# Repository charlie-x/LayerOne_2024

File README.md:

# LayerOne_2024
Repo for LayerOne 2024

# L1 Pov Spinner

## What is the Pov Spinner?

The Pov Spinner is an electronic fidget spinner that displays words and patterns via LED's when spinning. It was part of the LayerOne 2024 Conference badge.

## What is needed to change the code on the Spinner?

* Code from repo
* Computer
* AVR programming device
* Build software
* Flash software
* Device drivers

# Code from repo

Clone the git repo or download the zip of the repo

## git clone
```
git clone https://github.com/charlie-x/LayerOne_2024.git
```

## Download zip

```
wget https://github.com/charlie-x/LayerOne_2024/archive/refs/heads/main.zip
```

## Edit the code

Open the **L12024POV.cproj** project file.

The text and animation code is located in **main.c**.

Once the desired changes are complete, run the **build**. This will output the build files into the **Debug** folder.  

The **L12024POV.hex** file created is what will be used to flash the spinner.

## AVR programing device

**NOTE: Any AVR programmer should work.**

The LayerOne attendees were able to obtain a **Kraken** AVR programmer to use for this purpose which is an avrisp/mkii/avr dragon/usbasp.

Kraken based on this board: 

https://www.fischl.de/usbasp/

### Arduino as an AVR programmer

Alternatively, and Ardunio can be used to program the device:

https://docs.arduino.cc/built-in-examples/arduino-isp/ArduinoISP/

https://www.amazon.com/CANADUINO-USBtinyISP-Programmer-Compatible-Arduino/dp/B0751LJH3Z

## Build Software

Either use Microchip Studio or avr-gcc to build it.

### *nix

Install **avr-gcc** via the **gcc-avr** package

sudo apt-get install binutils gcc-avr avr-libc uisp avrdude flex byacc bison

### Windows

https://www.microchip.com/en-us/tools-resources/develop/microchip-studio

### Mac

port

https://ports.macports.org/port/avr-gcc/

homebrew

https://github.com/osx-cross/homebrew-avr

for avr-gcc's use the makefile

## Flashing the board

**NOTE: The kraken needs avrdude, it is not supported in microchip studio.**

### *nix / Windows / Mac - avrdude

AVRDUDE - is a program for downloading and uploading the on-chip memories of Microchip’s AVR microcontrollers.

Flash the board with the compiled **hex** file to device

https://github.com/avrdudes/avrdude/releases

```
avrdude -c usbasp -p t4313 -v -B 3 -U flash:w:..\LayerOne_2024-main\LayerOne_2024-main\L1_POVSpinner\L12024POV\Debug\L12024POV.hex
```

### Windows - atprogram

atprogram - is a program that comes with Microchip Studio

```
atprogram -cl 200khz -v -d attiny4313 -t atmelice -i isp chiperase
atprogram -cl 200khz -v -d attiny4313 -t atmelice -i isp program -f L12024POV\Release\L12024POV.elf
```

#### Device Drivers for Windows

Zadig is a Windows application that installs generic USB drivers, such as WinUSB, libusb-win32/libusb0.sys or libusbK, to help you access USB devices that can be found here:
https://zadig.akeo.ie/#

Install the **libusbK** driver

## Spinner Pinouts for programming

The device has the Ground pin labeld as **G**. 

## Notes on modifiying the code

The image folder are made of 12xN high 1 bit png's and the imageConvert tool spits them out as a header file, just include them and use drawImage

imageConvert <in.png> <out.h> <label>

use <label> to pass into drawImage use #include <out.h> (with the right name) in the main.c

interrupt driven from a hall effect sensor, triggers the loops to draw and calcs an RPM then it goes into sleep after the effect is drawn, the hall effect can wake it up, but to save battery pressing the button wakes the cpu up again

the slider switch needs to be be in the furthest away position from the programming pads, match the G to gnd on the programmer..

==============================================================================

calculate x/y

30 is 360/nuber of leds around, which is speed dependant  so used the number of leds vertically

  angle_radians = ( led_number * 30 *pi / 180  )

  x_inner = radius * cos ( angle_radius )
  y_inner = radius * cos ( angle_radius )

distance...

  distance = sqrt( (dx^2) + (dy^2))

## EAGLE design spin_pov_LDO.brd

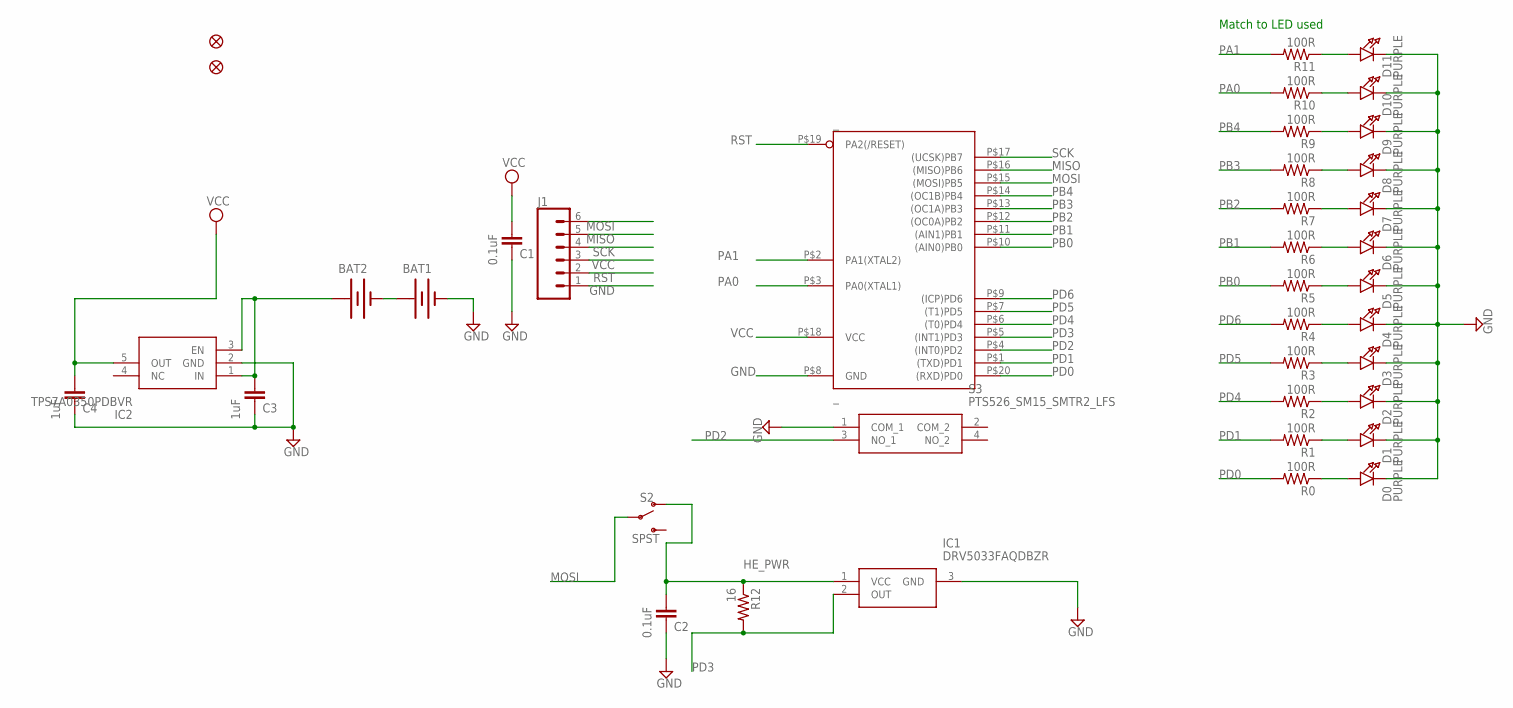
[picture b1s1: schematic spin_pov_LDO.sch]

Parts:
AFID1, AFID2: FIDUCIAL""; FIDUCIAL_1MM
BAT1, BAT2: SPARKFUN_BATTERYSPARKFUN_BATTCOMM_20MM_LINX; SPARKFUN_BATTCOM_20MM_LINX
C1, C2: 0.1uF; 0805
C3, C4: 1uF; 0805
D0, D1, D2, D3, D4, D5, D6, D7, D8, D9, D10, D11: PURPLE; CHIPLED_0805_NOOUTLINE
IC1: DRV5033FAQDBZR; SOT95P237X112-3N
IC2: TPS7A0350PDBVR; SOT95P280X145-5N
J1: CONN_06SMD-FEMALE-V2; 1X06-SMD-FEMALE
R0, R1, R2, R3, R4, R5, R6, R7, R8, R9, R10, R11: 100R; 0805
R12: 16; 0805
S2: SPST; SWITCH_SPST_SMD_A
S3: PTS526_SM15_SMTR2_LFS; PTS526SM15SMTR2LFS
_: _; MLF20

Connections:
GND: BAT1.2 (-), C1.2, C2.2, C3.2, C4.2, D0.C, D1.C, D2.C, D3.C, D4.C, D5.C, D6.C, D7.C, D8.C, D9.C, D10.C, D11.C, IC1.3 (GND), IC2.2 (GND), J1.1, S3.1 (COM_1), _.P$8 (GND)
HE_PWR: C2.1, IC1.1 (VCC), R12.1, S2.1 (O)
MISO: J1.5, _.P$16 ((MISO)PB6)
MOSI: J1.6, S2.2, _.P$15 ((MOSI)PB5)
unnamed: BAT2.1 (+), C3.1, IC2.1 (IN), IC2.3 (EN)
unnamed: BAT1.1 (+), BAT2.2 (-)
unnamed: D0.A, R0.1
unnamed: D1.A, R1.1
unnamed: D2.A, R2.1
unnamed: D3.A, R3.1
unnamed: D4.A, R4.1
unnamed: D5.A, R5.1
unnamed: D6.A, R6.1
unnamed: D7.A, R7.1
unnamed: D8.A, R8.1
unnamed: D9.A, R9.1
unnamed: D10.A, R10.1
unnamed: D11.A, R11.1
PA0: R10.2, _.P$3 (PA0(XTAL1))
PA1: R11.2, _.P$2 (PA1(XTAL2))
PB0: R5.2, _.P$10 ((AIN0)PB0)
PB1: R6.2, _.P$11 ((AIN1)PB1)
PB2: R7.2, _.P$12 ((OC0A)PB2)
PB3: R8.2, _.P$13 ((OC1A)PB3)
PB4: R9.2, _.P$14 ((OC1B)PB4)
PD0: R0.2, _.P$20 ((RXD)PD0)
PD1: R1.2, _.P$1 ((TXD)PD1)
PD2: S3.3 (NO_1), _.P$4 ((INT0)PD2)
PD3: IC1.2 (OUT), R12.2, _.P$5 ((INT1)PD3)
PD4: R2.2, _.P$6 ((T0)PD4)
PD5: R3.2, _.P$7 ((T1)PD5)
PD6: R4.2, _.P$9 ((ICP)PD6)
RST: J1.2, _.P$19 (PA2(/RESET))
SCK: J1.4, _.P$17 ((UCSK)PB7)
VCC: C1.1, C4.1, IC2.5 (OUT), J1.3, _.P$18 (VCC)

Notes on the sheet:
Match to LED used

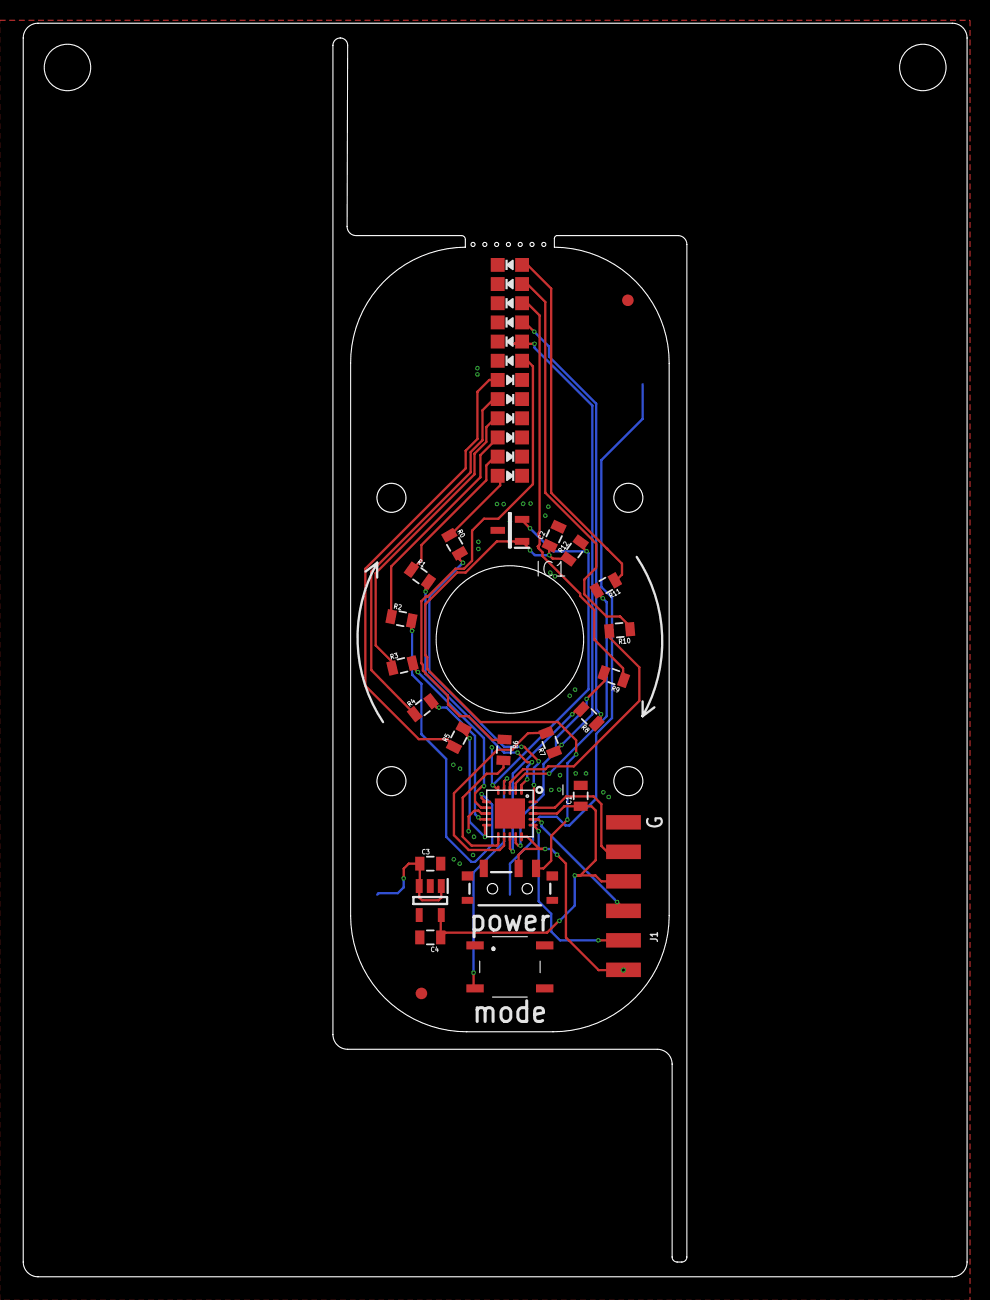
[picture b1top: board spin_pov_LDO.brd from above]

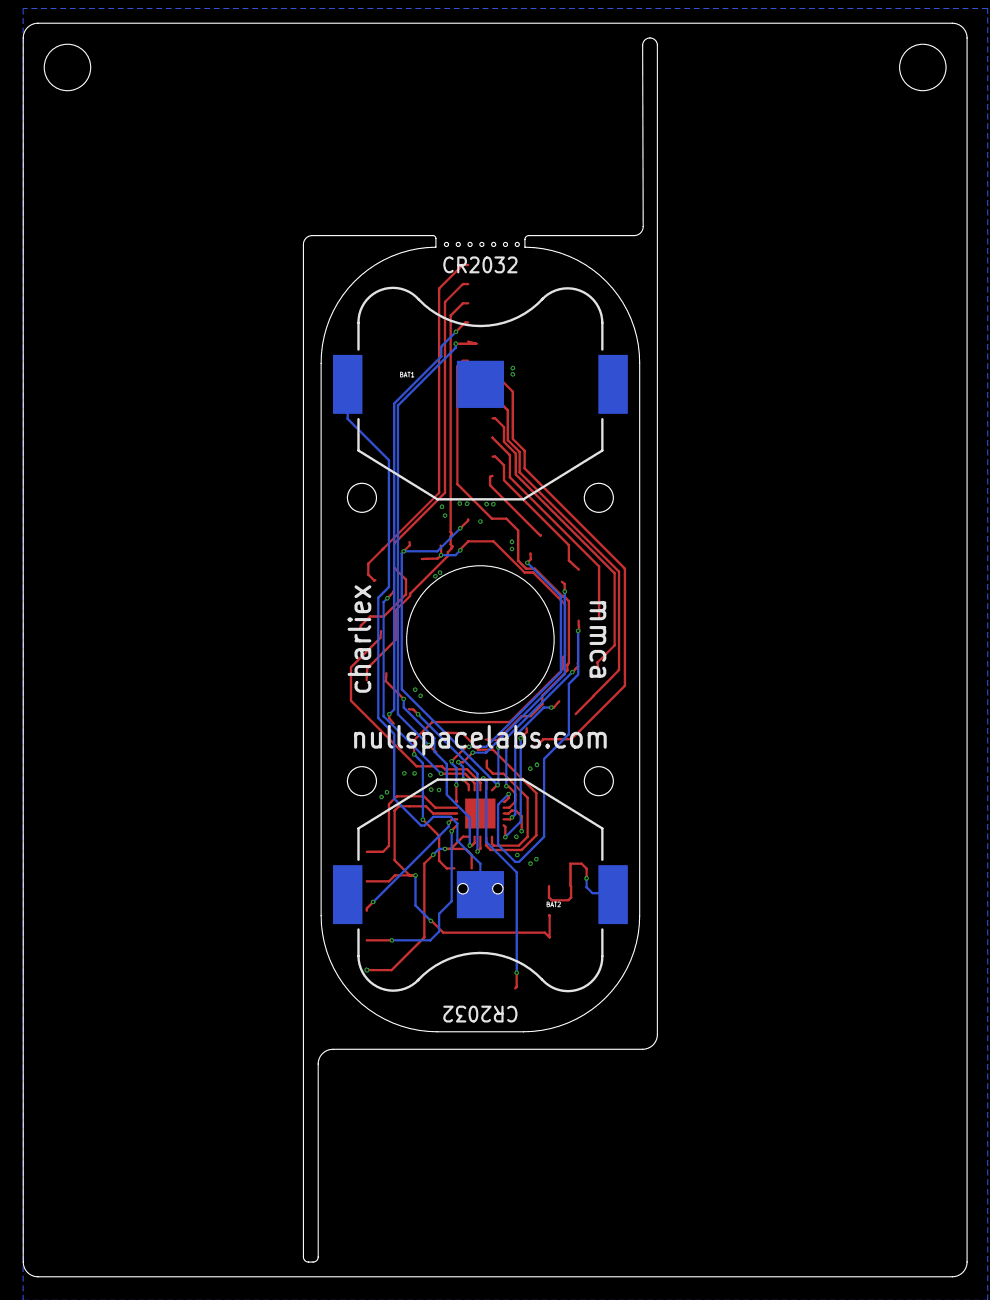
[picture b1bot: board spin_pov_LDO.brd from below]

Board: 2 copper layers, 81.2 x 107.8 mm, 39 parts (2 on the bottom side), 35 nets.

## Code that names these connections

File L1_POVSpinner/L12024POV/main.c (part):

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#define LED_PORT					PORTA
#define LED_DDR						DDRA

#define BUTTON						PD2
#define HALL_EFFECT_POWER			PB5

#define BIT_SET(port, bit)			((port) |= (1 << (bit)))
#define BIT_CLEAR(port, bit)		((port) &= ~(1 << (bit)))
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
	#define inv  (11)
	
	if (BIT_TEST(mask,inv -  0) ) BIT_SET( PORTD, PD0) ; else BIT_CLEAR (PORTD , PD0);
	if (BIT_TEST(mask,inv -  1) ) BIT_SET( PORTD, PD1) ; else BIT_CLEAR (PORTD , PD1);
	if (BIT_TEST(mask,inv -  2) ) BIT_SET( PORTD, PD4) ; else BIT_CLEAR (PORTD , PD4);
	if (BIT_TEST(mask,inv -  3) ) BIT_SET( PORTD, PD5) ; else BIT_CLEAR (PORTD , PD5);
	if (BIT_TEST(mask,inv -  4) ) BIT_SET( PORTD, PD6) ; else BIT_CLEAR (PORTD , PD6);
	if (BIT_TEST(mask,inv -  5) ) BIT_SET( PORTB, PB0) ; else BIT_CLEAR (PORTB , PB0);
	if (BIT_TEST(mask,inv -  6) ) BIT_SET( PORTB, PB1) ; else BIT_CLEAR (PORTB , PB1);
	if (BIT_TEST(mask,inv -  7) ) BIT_SET( PORTB, PB2) ; else BIT_CLEAR (PORTB , PB2);
	if (BIT_TEST(mask,inv -  8) ) BIT_SET( PORTB, PB3) ; else BIT_CLEAR (PORTB , PB3);
	if (BIT_TEST(mask,inv -  9) ) BIT_SET( PORTB, PB4) ; else BIT_CLEAR (PORTB , PB4);
	if (BIT_TEST(mask,inv - 10) ) BIT_SET( PORTA, PA0) ; else BIT_CLEAR (PORTA , PA0);
	if (BIT_TEST(mask,inv - 11) ) BIT_SET( PORTA, PA1) ; else BIT_CLEAR (PORTA , PA1);
	#undef inv
}

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	//PRR &= ~(1 << PRTIM1); // Ensure Timer1 is enabled

	// set led pins as output
	DDRA |= 0b00000011;				// for PA1 and PA0
	DDRB |= 0b00111111;				// for PB4 to PB0 and pb5 for mosi
	DDRD |= 0b01110011;				// for PD6, PD5, PD4, PD1 and PD0
	
	//power up mosi
	BIT_SET( PORTB, PB5);
	
	// we're on the saving bytes route
	// set hall effect sensor pin PD3 as input
	//DDRD &= ~(1 << PD3);
	
	// button
	//DDRD &= ~(1 << BUTTON);			// set as input
	PORTD |= (1 << BUTTON);			// enable internal pull-up resistor

	// Configure external interrupt for button PD2
	// Set the interrupt to trigger wake mode
	//	MCUCR |=  (1 << ISC01);
	//	MCUCR &= ~(1 << ISC01);
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	//	GIMSK |= (1 << INT0);			// Enable INT0
	GIMSK |= (1 << INT0) | (1 << INT1);

	// enable external interrupt on PD3 (combine to previous)
	MCUCR |= (1 << ISC11);			// trigger on rising edge only
	MCUCR &= ~(1 << ISC10);

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		sei();
		
		//power down mosi
		BIT_CLEAR( PORTB, PB5);
		
		isSleeping = true;
		sleep_cpu();
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	powerDownCountdown = COUNTDOWN_LENGTH;
	
	//power up MOSI and the hall effect sensor
	BIT_SET( PORTB, PB5);
	
	sleep_enable();
}
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			setLEDS(0xaa);
			
			// turn off MOSI
			BIT_CLEAR( PORTB, PB5);
			_delay_ms(50);
			
			powerDownCountdown = COUNTDOWN_LENGTH;
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
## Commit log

2024-05-26 Add files via upload
    added 3mf's for case
2024-05-27 Update Makefile for Unix
    Optimized compiling
2024-05-28 Update README.md
    Update to readme.
2024-05-28 Update README.md
    Updated Flashing the board section.
2024-05-28 Addition of docs folder and images
2024-05-28 Update README.md
    Addition of zadig_libusbK.png
2024-05-28 Addition of images
2024-05-28 Update README.md - Addition of images
    Added pinout, microchip studio and spinner images
2024-05-28 Update README.md
    Update of avrdude line
2024-05-28 added eagle files for badge.
2024-05-28 Update of spinner image
2024-05-28 Addition of new spinner image

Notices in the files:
parts and their libraries:
SparkFun-Connectors: Licensing: Creative Commons ShareAlike 4.0 International - https://creativecommons.org/licenses/by-sa/4.0
microbuilder: This work is placed in the public domain, and may be freely used for commercial and non-commercial work with the following conditions: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
